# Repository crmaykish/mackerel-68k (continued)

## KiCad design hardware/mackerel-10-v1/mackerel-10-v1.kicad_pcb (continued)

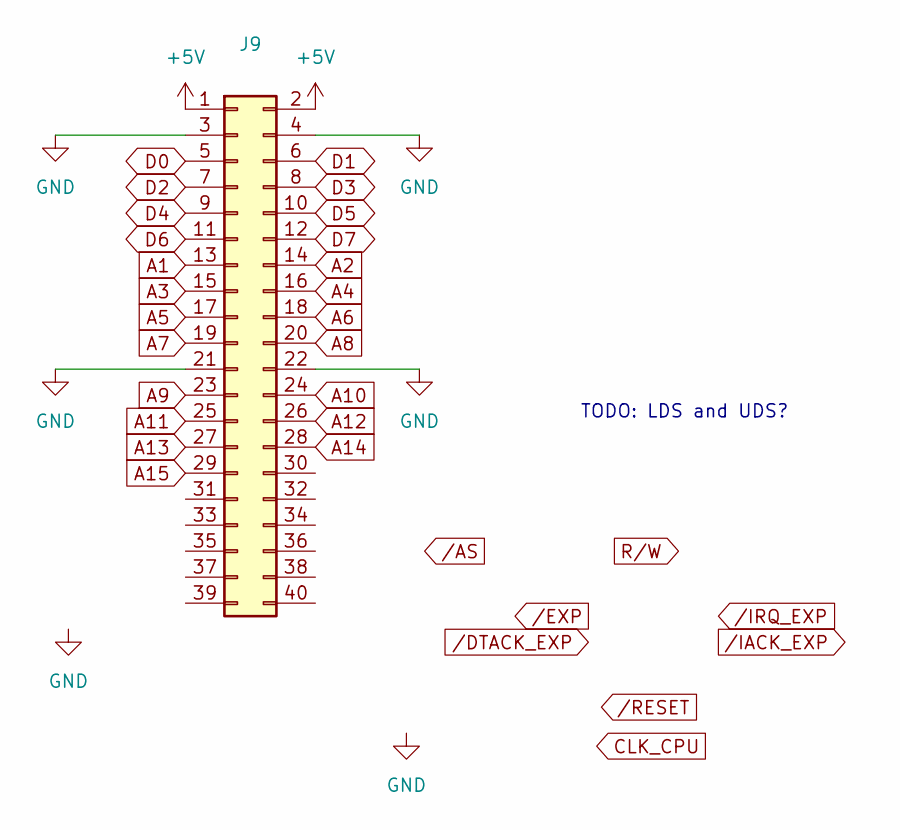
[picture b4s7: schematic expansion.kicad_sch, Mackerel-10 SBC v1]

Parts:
J9: Conn_02x20_Odd_Even; IDC-Header_2x20_P2.54mm_Vertical

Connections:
+5V: J9.1, J9.2; also elsewhere on the board
A1: J9.13; also elsewhere on the board
A2: J9.14; also elsewhere on the board
A3: J9.15; also elsewhere on the board
A4: J9.16; also elsewhere on the board
A5: J9.17; also elsewhere on the board
A6: J9.18; also elsewhere on the board
A7: J9.19; also elsewhere on the board
A8: J9.20; also elsewhere on the board
A9: J9.23; also elsewhere on the board
A10: J9.24; also elsewhere on the board
A11: J9.25; also elsewhere on the board
A12: J9.26; also elsewhere on the board
A13: J9.27; also elsewhere on the board
A14: J9.28; also elsewhere on the board
A15: J9.29; also elsewhere on the board
D0: J9.5; also elsewhere on the board
D1: J9.6; also elsewhere on the board
D2: J9.7; also elsewhere on the board
D3: J9.8; also elsewhere on the board
D4: J9.9; also elsewhere on the board
D5: J9.10; also elsewhere on the board
D6: J9.11; also elsewhere on the board
D7: J9.12; also elsewhere on the board
GND: J9.3, J9.4, J9.21, J9.22; also elsewhere on the board

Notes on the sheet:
TODO: LDS and UDS?

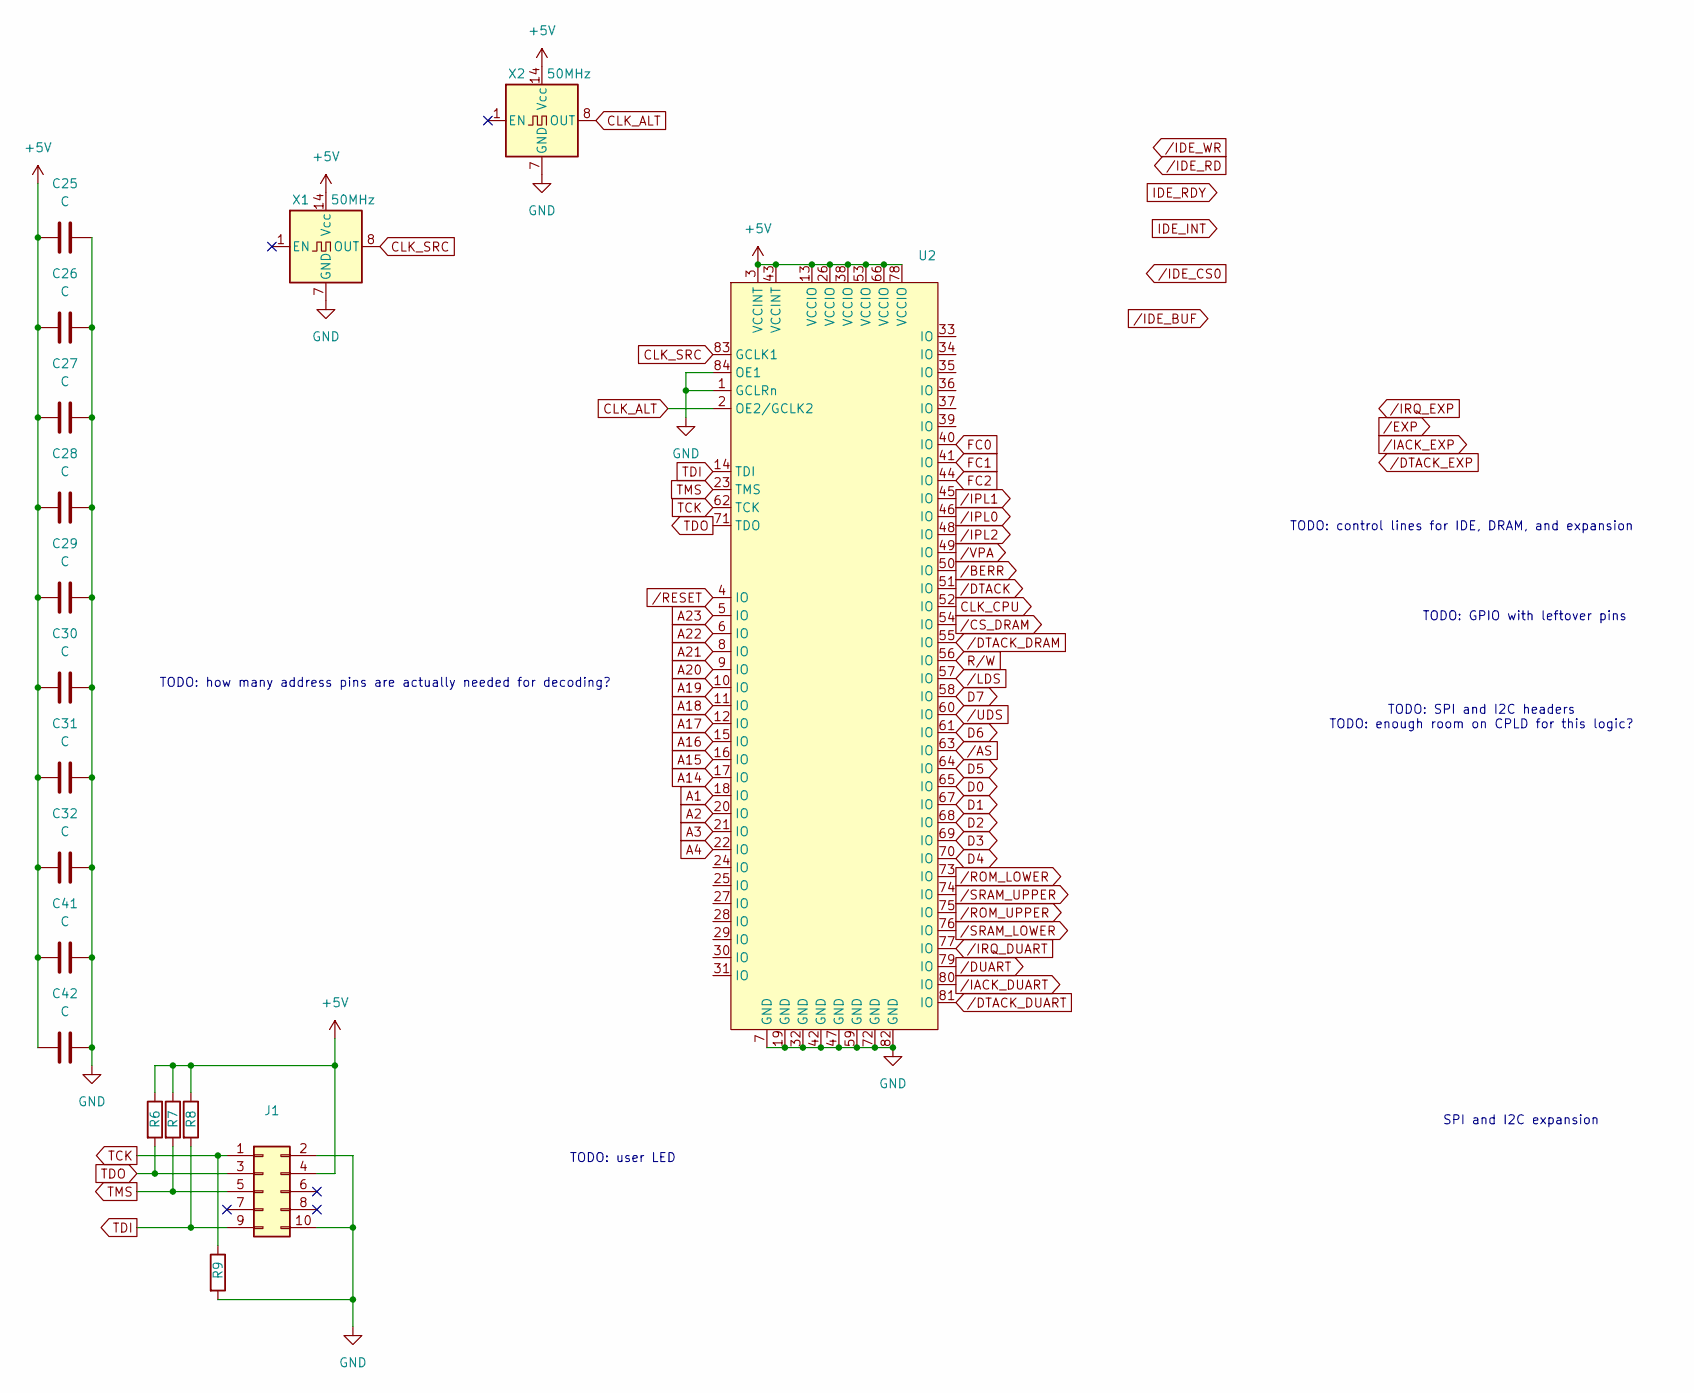
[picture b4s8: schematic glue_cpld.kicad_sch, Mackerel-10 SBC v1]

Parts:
C25, C26, C27, C28, C29, C30, C31, C32, C41, C42: C; C_Disc_D4.3mm_W1.9mm_P5.00mm
J1: Conn_02x05_Odd_Even; IDC-Header_2x05_P2.54mm_Vertical
R6, R7, R8, R9: R; R_Axial_DIN0207_L6.3mm_D2.5mm_P7.62mm_Horizontal
U2: PLCC-84_THT-Socket
X1, X2: 50MHz; Oscillator_DIP-14

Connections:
+5V: C25.1, C26.1, C27.1, C28.1, C29.2, C30.2, C31.2, C32.2, C41.2, C42.2, J1.4, R6.1, R7.1, R8.1, U2.3 (VCCINT), U2.13 (VCCIO), U2.26 (VCCIO), U2.38 (VCCIO), U2.43 (VCCINT), U2.53 (VCCIO), U2.66 (VCCIO), U2.78 (VCCIO), X1.14 (Vcc), X2.14 (Vcc); also elsewhere on the board
A1: U2.18 (IO); also elsewhere on the board
A2: U2.20 (IO); also elsewhere on the board
A3: U2.21 (IO); also elsewhere on the board
A4: U2.22 (IO); also elsewhere on the board
A14: U2.17 (IO); also elsewhere on the board
A15: U2.16 (IO); also elsewhere on the board
A16: U2.15 (IO); also elsewhere on the board
A17: U2.12 (IO); also elsewhere on the board
A18: U2.11 (IO); also elsewhere on the board
A19: U2.10 (IO); also elsewhere on the board
A20: U2.9 (IO); also elsewhere on the board
A21: U2.8 (IO); also elsewhere on the board
A22: U2.6 (IO); also elsewhere on the board
A23: U2.5 (IO); also elsewhere on the board
CLK_ALT: U2.2 (OE2/GCLK2), X2.8 (OUT); also elsewhere on the board
CLK_CPU: U2.52 (IO); also elsewhere on the board
CLK_SRC: U2.83 (GCLK1), X1.8 (OUT); also elsewhere on the board
D0: U2.65 (IO); also elsewhere on the board
D1: U2.67 (IO); also elsewhere on the board
D2: U2.68 (IO); also elsewhere on the board
D3: U2.69 (IO); also elsewhere on the board
D4: U2.70 (IO); also elsewhere on the board
D5: U2.64 (IO); also elsewhere on the board
D6: U2.61 (IO); also elsewhere on the board
D7: U2.58 (IO); also elsewhere on the board
FC0: U2.40 (IO); also elsewhere on the board
FC1: U2.41 (IO); also elsewhere on the board
FC2: U2.44 (IO); also elsewhere on the board
GND: C25.2, C26.2, C27.2, C28.2, C29.1, C30.1, C31.1, C32.1, C41.1, C42.1, J1.2, J1.10, R9.2, U2.1 (GCLRn), U2.7 (GND), U2.19 (GND), U2.32 (GND), U2.42 (GND), U2.47 (GND), U2.59 (GND), U2.72 (GND), U2.82 (GND), U2.84 (OE1), X1.7 (GND), X2.7 (GND); also elsewhere on the board
R/W: U2.56 (IO); also elsewhere on the board
TCK: J1.1, R9.1, U2.62 (TCK)
TDI: J1.9, R8.2, U2.14 (TDI)
TDO: J1.3, R6.2, U2.71 (TDO)
TMS: J1.5, R7.2, U2.23 (TMS)
/AS: U2.63 (IO); also elsewhere on the board
/BERR: U2.50 (IO); also elsewhere on the board
/CS_DRAM: U2.54 (IO); also elsewhere on the board
/DTACK: U2.51 (IO); also elsewhere on the board
/DTACK_DRAM: U2.55 (IO); also elsewhere on the board
/DTACK_DUART: U2.81 (IO); also elsewhere on the board
/DUART: U2.79 (IO); also elsewhere on the board
/IACK_DUART: U2.80 (IO); also elsewhere on the board
/IPL0: U2.46 (IO); also elsewhere on the board
/IPL1: U2.45 (IO); also elsewhere on the board
/IPL2: U2.48 (IO); also elsewhere on the board
/IRQ_DUART: U2.77 (IO); also elsewhere on the board
/LDS: U2.57 (IO); also elsewhere on the board
/RESET: U2.4 (IO); also elsewhere on the board
/ROM_LOWER: U2.73 (IO); also elsewhere on the board
/ROM_UPPER: U2.75 (IO); also elsewhere on the board
/SRAM_LOWER: U2.76 (IO); also elsewhere on the board
/SRAM_UPPER: U2.74 (IO); also elsewhere on the board
/UDS: U2.60 (IO); also elsewhere on the board
/VPA: U2.49 (IO); also elsewhere on the board

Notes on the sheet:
TODO: how many address pins are actually needed for decoding?
SPI and I2C expansion
TODO: SPI and I2C headers TODO: enough room on CPLD for this logic?
TODO: GPIO with leftover pins
TODO: user LED
TODO: control lines for IDE, DRAM, and expansion

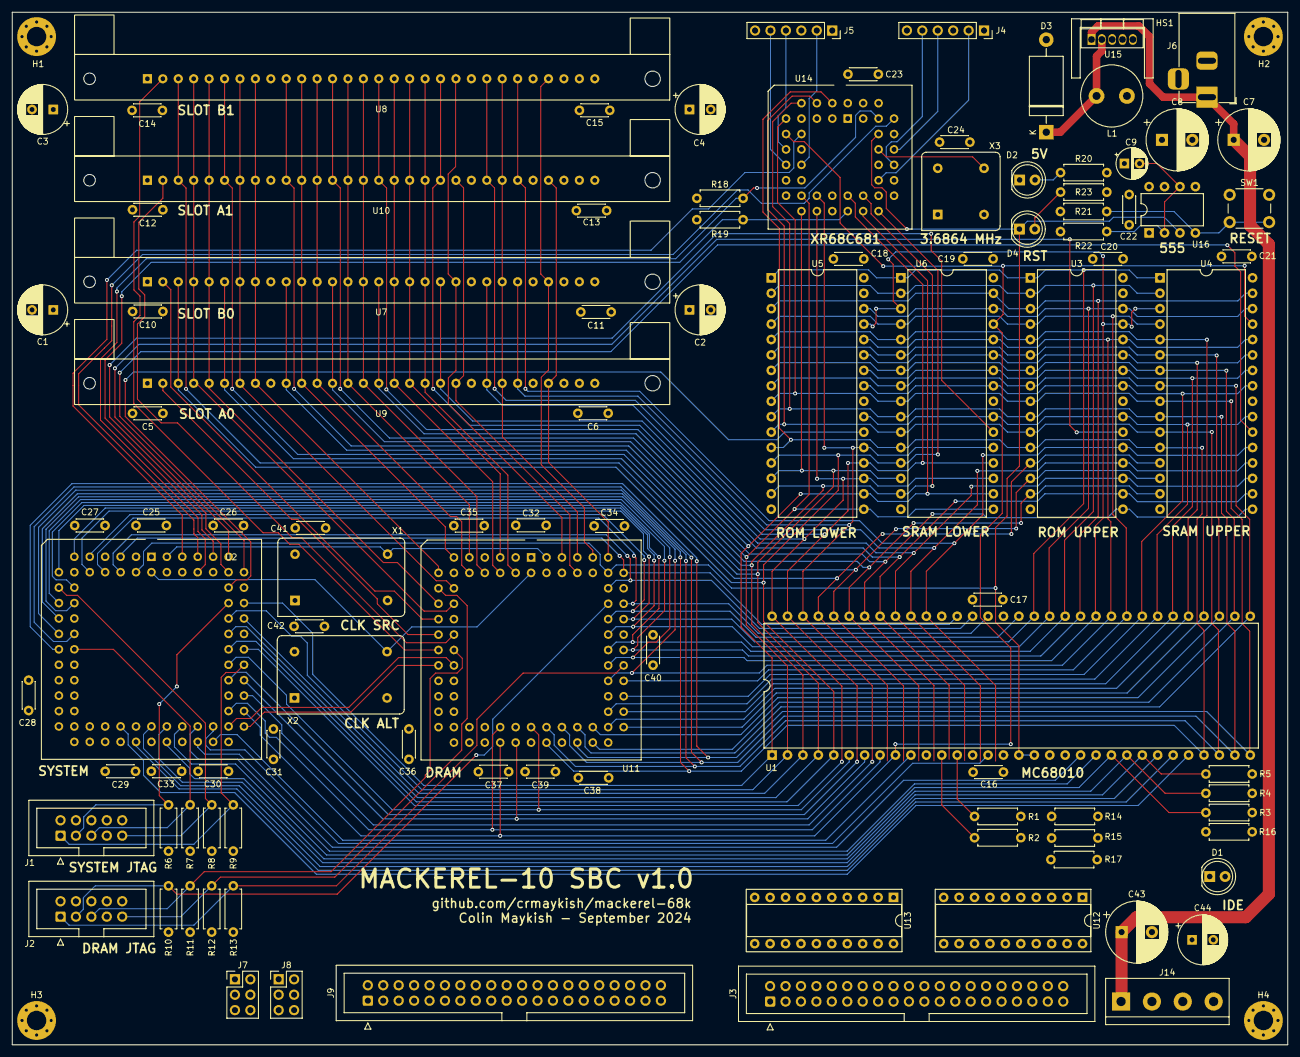
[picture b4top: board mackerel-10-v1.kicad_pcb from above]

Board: 4 copper layers, 210.0 x 170.0 mm, 107 parts (0 on the bottom side), 133 nets.

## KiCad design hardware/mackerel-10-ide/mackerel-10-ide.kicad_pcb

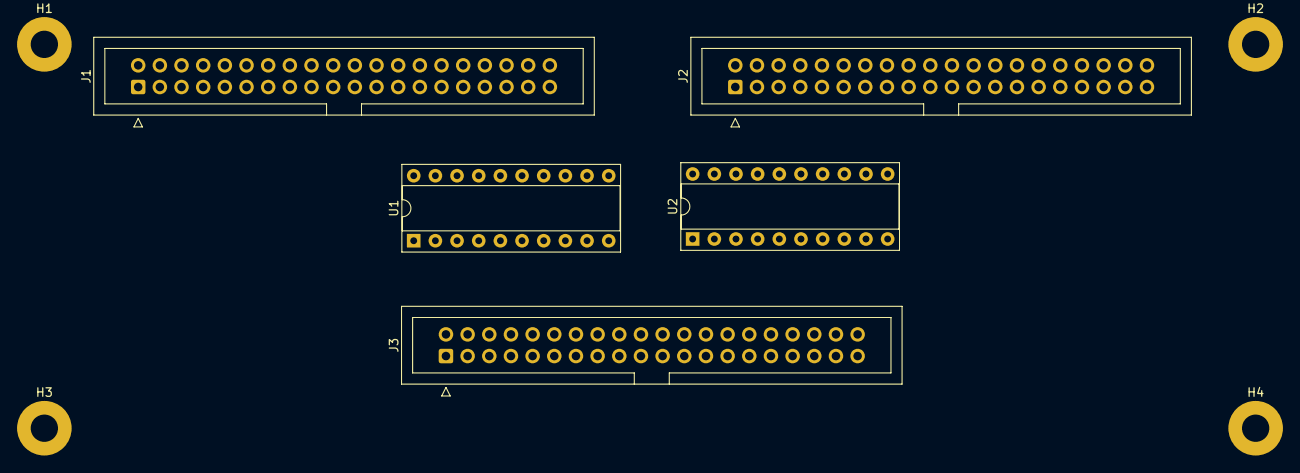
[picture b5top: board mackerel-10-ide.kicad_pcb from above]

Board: 2 copper layers, 9 parts (0 on the bottom side), 40 nets, no tracks yet.

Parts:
H1, H2, H3, H4: MountingHole_Pad; MountingHole_3.2mm_M3_Pad
J1, J2, J3: Conn_02x20_Odd_Even; IDC-Header_2x20_P2.54mm_Vertical
U1, U2: 74HC245; DIP-20_W7.62mm_Socket

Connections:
+5V: J1.1, J1.2, J2.1, J2.2, U1.20 (VCC), U2.20 (VCC)
A1: J1.13, J3.35
A2: J1.14, J3.33
A3: J1.15, J3.36
D0: J2.5, U2.2 (A0)
D1: J2.6, U2.3 (A1)
D2: J2.7, U2.4 (A2)
D3: J2.8, U2.5 (A3)
D4: J2.9, U2.6 (A4)
D5: J2.10, U2.7 (A5)
D6: J2.11, U2.8 (A6)
D7: J2.12, U2.9 (A7)
D8: J1.5, U1.9 (A7)
D9: J1.6, U1.8 (A6)
D10: J1.7, U1.7 (A5)
D11: J1.8, U1.6 (A4)
D12: J1.9, U1.5 (A3)
D13: J1.10, U1.4 (A2)
D14: J1.11, U1.3 (A1)
D15: J1.12, U1.2 (A0)
GND: H1.1, H2.1, H3.1, H4.1, J1.3, J1.4, J1.21, J1.22, J1.38, J1.39, J1.40, J2.3, J2.4, J2.23, J2.24, J2.33, J2.34, J2.39, J2.40, J3.2, J3.19, J3.22, J3.24, J3.26, J3.30, J3.40, U1.10 (GND), U2.10 (GND)
IDE_D0: J3.17, U1.11 (B7)
IDE_D1: J3.15, U1.12 (B6)
IDE_D2: J3.13, U1.13 (B5)
IDE_D3: J3.11, U1.14 (B4)
IDE_D4: J3.9, U1.15 (B3)
IDE_D5: J3.7, U1.16 (B2)
IDE_D6: J3.5, U1.17 (B1)
IDE_D7: J3.3, U1.18 (B0)
IDE_D8: J3.4, U2.18 (B0)
IDE_D9: J3.6, U2.17 (B1)
IDE_D10: J3.8, U2.16 (B2)
IDE_D11: J3.10, U2.15 (B3)
IDE_D12: J3.12, U2.14 (B4)
IDE_D13: J3.14, U2.13 (B5)
IDE_D14: J3.16, U2.12 (B6)
IDE_D15: J3.18, U2.11 (B7)
R/W: J2.14, U1.1 (A->B), U2.1 (A->B)
/IDE_BUF: U1.19 (CE), U2.19 (CE)
/RESET: J2.37, J2.38, J3.1

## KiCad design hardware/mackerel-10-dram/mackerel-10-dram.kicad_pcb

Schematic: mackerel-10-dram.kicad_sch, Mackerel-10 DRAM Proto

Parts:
C1, C2: 1000uF; CP_Radial_D8.0mm_P3.50mm
C3, C4, C5, C6, C7, C8, C9, C10: 0.1uF; C_Disc_D4.7mm_W2.5mm_P5.00mm
D1: LED; LED_D5.0mm
H1, H2, H3, H4: MountingHole_Pad; MountingHole_3.2mm_M3_Pad
J1, J2: Conn_02x20_Odd_Even; IDC-Header_2x20_P2.54mm_Vertical
J3: Conn_02x05_Odd_Even; IDC-Header_2x05_P2.54mm_Vertical
J4, J5: Conn_01x30; PinHeader_1x30_P2.54mm_Vertical
J6: Conn_01x10; PinSocket_1x10_P2.54mm_Vertical
R1, R2, R3, R4, R5: R; R_Axial_DIN0207_L6.3mm_D2.5mm_P7.62mm_Horizontal
R6, R7, R8, R9, R10, R11, R12, R13, R14, R15, R16, R17, R18, R19, R20, R21: 22; R_Axial_DIN0207_L6.3mm_D2.5mm_P2.54mm_Vertical
U1, U2: SIMM-30
U3: PLCC-84_THT-Socket

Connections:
+5V: C1.1, C2.1, C3.1, C4.1, C5.1, C6.1, C7.1, C8.1, C9.1, C10.1, J1.1, J1.2, J2.1, J2.2, J3.4, J4.1, J4.30, J5.1, J5.30, J6.9, R1.1, R2.1, R3.1, R5.1, U1.1 (VCC), U1.30 (VCC), U2.1 (VCC), U2.30 (VCC), U3.3 (VCCINT), U3.13 (VCCIO), U3.26 (VCCIO), U3.38 (VCCIO), U3.43 (VCCINT), U3.53 (VCCIO), U3.66 (VCCIO), U3.78 (VCCIO)
A1: J1.13, U3.52 (IO)
A2: J1.14, U3.51 (IO)
A3: J1.15, U3.50 (IO)
A4: J1.16, U3.49 (IO)
A5: J1.17, U3.48 (IO)
A6: J1.18, U3.46 (IO)
A7: J1.19, U3.45 (IO)
A8: J1.20, U3.44 (IO)
A9: J1.27, U3.12 (IO)
A10: J1.28, U3.15 (IO)
A11: J1.29, U3.11 (IO)
A12: J1.30, U3.9 (IO)
A13: J1.31, U3.10 (IO)
A14: J1.32, U3.8 (IO)
A15: J1.33, U3.5 (IO)
A16: J1.34, U3.6 (IO)
A17: J1.35, U3.4 (IO)
A18: J1.36, U3.81 (IO)
A19: J1.37, U3.79 (IO)
A20: J1.26, U3.17 (IO)
A21: J1.25, U3.16 (IO)
A22: J1.24, U3.18 (IO)
A23: J1.23, U3.21 (IO)
CAS0: J4.2, U1.2 (/CAS), U3.55 (IO)
CAS1: J5.2, U2.2 (/CAS), U3.56 (IO)
CLK_CPU: J2.35
CLK_SRC: J2.36, U3.83 (GCLK1)
D0: J2.5, R13.2
D1: J2.6, R12.2
D2: J2.7, R11.2
D3: J2.8, R10.2
D4: J2.9, R9.2
D5: J2.10, R8.2
D6: J2.11, R7.2
D7: J2.12, R6.2
D8: J1.5, R14.2
D9: J1.6, R15.2
D10: J1.7, R16.2
D11: J1.8, R17.2
D12: J1.9, R18.2
D13: J1.10, R19.2
D14: J1.11, R20.2
D15: J1.12, R21.2
GND: C1.2, C2.2, C3.2, C4.2, C5.2, C6.2, C7.2, C8.2, C9.2, C10.2, D1.1 (K), H1.1, H2.1, H3.1, H4.1, J1.3, J1.4, J1.21, J1.22, J1.38, J1.39, J1.40, J2.3, J2.4, J2.23, J2.24, J2.33, J2.34, J2.39, J2.40, J3.2, J3.10, J4.9, J4.22, J5.9, J5.22, J6.10, R4.2, U1.9 (GND), U1.22 (GND), U2.9 (GND), U2.22 (GND), U3.1 (GCLRn), U3.2 (OE2/GCLK2), U3.7 (GND), U3.19 (GND), U3.32 (GND), U3.42 (GND), U3.47 (GND), U3.59 (GND), U3.72 (GND), U3.82 (GND), U3.84 (OE1)
GPIO_0: J2.25
GPIO_1: J2.26
GPIO_2: J2.27
GPIO_3: J2.28
GPIO_4: J2.29
GPIO_5: J2.30
GPIO_6: J2.31
GPIO_7: J2.32
unnamed: D1.2 (A), R5.2
unnamed: J6.1, U3.22 (IO)
unnamed: J6.2, U3.24 (IO)
unnamed: J6.3, U3.25 (IO)
unnamed: J6.4, U3.27 (IO)
unnamed: J6.5, U3.28 (IO)
unnamed: J6.6, U3.29 (IO)
unnamed: J6.7, U3.30 (IO)
unnamed: J6.8, U3.31 (IO)
RAMWR: J4.21, J5.21, U1.21 (/WE), U2.21 (/WE), U3.57 (IO)
RAM_A0: J4.4, J5.4, U1.4 (A0), U2.4 (A0), U3.58 (IO)
RAM_A1: J4.5, J5.5, U1.5 (A1), U2.5 (A1), U3.60 (IO)
RAM_A2: J4.7, J5.7, U1.7 (A2), U2.7 (A2), U3.61 (IO)
RAM_A3: J4.8, J5.8, U1.8 (A3), U2.8 (A3), U3.63 (IO)
RAM_A4: J4.11, J5.11, U1.11 (A4), U2.11 (A4), U3.64 (IO)
RAM_A5: J4.12, J5.12, U1.12 (A5), U2.12 (A5), U3.65 (IO)
RAM_A6: J4.14, J5.14, U1.14 (A6), U2.14 (A6), U3.67 (IO)
RAM_A7: J4.15, J5.15, U1.15 (A7), U2.15 (A7), U3.68 (IO)
RAM_A8: J4.17, J5.17, U1.17 (A8), U2.17 (A8), U3.69 (IO)
RAM_A9: J4.18, J5.18, U1.18 (A9), U2.18 (A9), U3.70 (IO)
RAM_A10: J4.19, J5.19, U1.19 (A10), U2.19 (A10), U3.73 (IO)
RAM_A11: J4.24, J5.24, U1.24 (A11), U2.24 (A11), U3.74 (IO)
RAM_D0: J4.3, R6.1, U1.3 (DQ0)
RAM_D1: J4.6, R7.1, U1.6 (DQ1)
RAM_D2: J4.10, R8.1, U1.10 (DQ2)
RAM_D3: J4.13, R9.1, U1.13 (DQ3)
RAM_D4: J4.16, R10.1, U1.16 (DQ4)
RAM_D5: J4.20, R11.1, U1.20 (DQ5)
RAM_D6: J4.23, R12.1, U1.23 (DQ6)
RAM_D7: J4.25, R13.1, U1.25 (DQ7)
RAM_D8: J5.3, R14.1, U2.3 (DQ0)
RAM_D9: J5.6, R15.1, U2.6 (DQ1)
RAM_D10: J5.10, R16.1, U2.10 (DQ2)
RAM_D11: J5.13, R17.1, U2.13 (DQ3)
RAM_D12: J5.16, R18.1, U2.16 (DQ4)
RAM_D13: J5.20, R19.1, U2.20 (DQ5)
RAM_D14: J5.23, R20.1, U2.23 (DQ6)
RAM_D15: J5.25, R21.1, U2.25 (DQ7)
RAS: J4.27, J5.27, U1.27 (/RAS), U2.27 (/RAS), U3.54 (IO)
R/W: J2.14, U3.76 (IO)
TCK: J3.1, R4.1, U3.62 (TCK)
TDI: J3.9, R3.2, U3.14 (TDI)
TDO: J3.3, R1.2, U3.71 (TDO)
TMS: J3.5, R2.2, U3.23 (TMS)
/AS: J2.13, U3.75 (IO)
/BERR: J2.17
/DTACK_EXP: J2.21, U3.40 (IO)
/EXP: J2.19, U3.41 (IO)
/IACK_EXP: J2.22
/IRQ_EXP: J2.20
/LDS: J2.16, U3.77 (IO)
/RESET: J2.37, J2.38, U3.20 (IO)
/UDS: J2.15, U3.80 (IO)
/VPA: J2.18

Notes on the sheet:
NOTE: data lines are reversed to facilitate routing

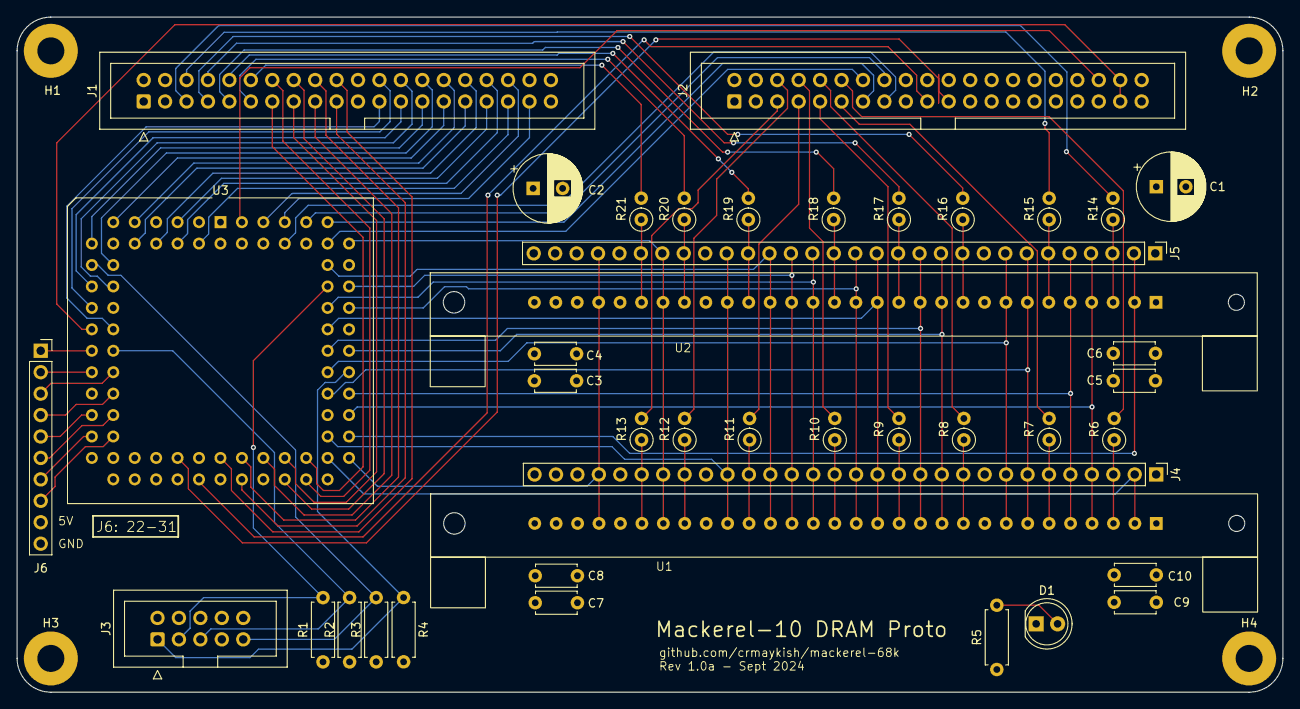
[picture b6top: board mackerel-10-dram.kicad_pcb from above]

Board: 4 copper layers, 150.0 x 80.0 mm, 45 parts (0 on the bottom side), 94 nets.

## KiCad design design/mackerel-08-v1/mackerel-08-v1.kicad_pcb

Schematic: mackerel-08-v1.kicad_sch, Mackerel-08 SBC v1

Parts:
J1: Conn_02x20_Odd_Even; IDC-Header_2x20_P2.54mm_Vertical
JP1: Jumper_2_Open; PinHeader_1x02_P2.54mm_Vertical
R1, R2, R3, R4, R5, R6, R7, R18, R19, R20: R; R_Axial_DIN0207_L6.3mm_D2.5mm_P7.62mm_Horizontal
U1: MC68008; PLCC-52_THT-Socket
U2: 74HC595; DIP-16_W7.62mm
U3, U4, U5: ATF22V10C; DIP-24_W7.62mm
X1: CXO_DIP8; Oscillator_DIP-8

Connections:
/CLK_CPU: U1.38 (CLK), X1.5 (OUT)
A0: J1.13, U1.51 (A0); also elsewhere on the board
A1: J1.14, U1.52 (A1), U4.10 (IN9); also elsewhere on the board
A2: J1.15, U1.1 (A2), U4.11 (IN10); also elsewhere on the board
A3: J1.16, U1.2 (A3), U4.13 (IN11); also elsewhere on the board
A4: J1.17, U1.3 (A4); also elsewhere on the board
A5: J1.18, U1.4 (A5); also elsewhere on the board
A6: J1.19, U1.5 (A6); also elsewhere on the board
A7: J1.20, U1.6 (A7); also elsewhere on the board
A8: J1.23, U1.7 (A8); also elsewhere on the board
A9: J1.24, U1.8 (A9); also elsewhere on the board
A10: J1.25, U1.9 (A10); also elsewhere on the board
A11: J1.26, U1.10 (A11); also elsewhere on the board
A12: J1.27, U1.11 (A12); also elsewhere on the board
A13: J1.28, U1.12 (A13), U3.4 (IN3/PD); also elsewhere on the board
A14: J1.29, U1.14 (A14), U3.5 (IN4); also elsewhere on the board
A15: J1.30, U1.16 (A15), U3.6 (IN5); also elsewhere on the board
A16: U1.18 (A16), U3.7 (IN6); also elsewhere on the board
A17: U1.19 (A17), U3.8 (IN7); also elsewhere on the board
A18: U1.20 (A18), U3.9 (IN8); also elsewhere on the board
A19: U1.21 (A19), U3.10 (IN9)
A20: U1.22 (A20), U3.11 (IN10)
A21: U1.13 (A21), U3.13 (IN11)
AS: U4.17 (IO3), U5.1 (CLK/IN0)
BOOT: U2.7 (QH), U3.1 (CLK/IN0)
D0: J1.5, U1.30 (D0); also elsewhere on the board
D1: J1.6, U1.29 (D1); also elsewhere on the board
D2: J1.7, U1.28 (D2); also elsewhere on the board
D3: J1.8, U1.27 (D3); also elsewhere on the board
D4: J1.9, U1.26 (D4); also elsewhere on the board
D5: J1.10, U1.25 (D5); also elsewhere on the board
D6: J1.11, U1.24 (D6); also elsewhere on the board
D7: J1.12, U1.23 (D7); also elsewhere on the board
FC0: U1.50 (FC0), U4.1 (CLK/IN0)
FC1: U1.49 (FC1), U4.2 (IN1)
FC2: U1.48 (FC2), U4.3 (IN2)
GND: J1.3, J1.4, J1.21, J1.22, J1.39, J1.40, R18.2, U1.17 (GND), U1.39 (GND), U2.8 (GND), U2.13 (~OE), U3.12 (GND), U4.7 (IN6), U4.8 (IN7), U4.9 (IN8), U4.12 (GND), U5.4 (IN3/PD), U5.10 (IN9), U5.11 (IN10), U5.12 (GND), U5.13 (IN11), X1.4 (GND); also elsewhere on the board
unnamed: JP1.1 (A), U5.23 (IO9)
unnamed: R6.1, U1.44 (/BERR)
unnamed: R5.1, U1.36 (/BGACK)
unnamed: R4.1, U1.37 (/BR)
unnamed: R7.1, U1.43 (/VPA)
/AS: J1.33, U1.31 (/AS), U2.11 (SRCLK), U2.12 (RCLK), U3.2 (IN1), U4.4 (IN3/PD)
/DS: J1.34, U1.32 (/DS)
/DTACK_CPU: JP1.2 (B), R18.1, U1.34 (/DTACK)
/DTACK_DUART: U5.6 (IN5); also elsewhere on the board
/DTACK_EXP: J1.37, U5.7 (IN6)
/DUART: U3.23 (IO9), U5.3 (IN2); also elsewhere on the board
/EXP: J1.35, U3.14 (IO0), U5.5 (IN4)
/IACK: U3.3 (IN2), U4.23 (IO9)
/IACK_DUART: U4.19 (IO5), U5.9 (IN8); also elsewhere on the board
/IACK_EXP: J1.38, U4.18 (IO4), U5.8 (IN7)
/IPL0: R1.2, U1.47 (/IPL0), U4.22 (IO8)
/IPL1: R2.2, U1.45 (/IPL1), U4.21 (IO7)
/IPL2: R3.2, U1.46 (/IPL2), U4.20 (IO6)
/IRQ_DUART: R19.2, U4.5 (IN4); also elsewhere on the board
/IRQ_EXP: J1.36, R20.2, U4.6 (IN5)
/RAM0: U3.21 (IO7); also elsewhere on the board
/RAM1: U3.20 (IO6); also elsewhere on the board
/RAM2: U3.19 (IO5); also elsewhere on the board
/RAM3: U3.18 (IO4); also elsewhere on the board
/RAM4: U3.17 (IO3); also elsewhere on the board
/RAM5: U3.16 (IO2); also elsewhere on the board
/RAM6: U3.15 (IO1); also elsewhere on the board
/RESET: J1.31, U1.40 (/HALT), U1.41 (/RESET), U2.10 (~SRCLR); also elsewhere on the board
/ROM: U3.22 (IO8), U5.2 (IN1); also elsewhere on the board
/RW: J1.32, U1.33 (/RW); also elsewhere on the board

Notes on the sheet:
Expansion Bus
DTACK Decoder / Wait States
MC68008 CPU
Inverted /AS
TODO: double check the pinout here
BOOT Signal
Interrupt Decoder
Address Decoder
Open for DTACK grounded Closed for DTACK control

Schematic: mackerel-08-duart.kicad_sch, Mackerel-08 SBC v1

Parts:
D1: LED; LED_D5.0mm
J2, J3: Conn_01x06; PinSocket_1x06_P2.54mm_Horizontal
J5, J6, J7: Conn_02x04_Odd_Even; IDC-Header_2x04_P2.54mm_Vertical
R8, R9, R10, R11, R12, R13, R28, R29: R; R_Axial_DIN0207_L6.3mm_D2.5mm_P7.62mm_Horizontal
U15: XR68C681; PLCC-44_THT-Socket
X2: CXO_DIP8; Oscillator_DIP-8

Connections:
A1: U15.2 (A1); also elsewhere on the board
A2: U15.4 (A2); also elsewhere on the board
A3: U15.6 (A3); also elsewhere on the board
A4: U15.7 (A4); also elsewhere on the board
D0: U15.28 (D0); also elsewhere on the board
D1: U15.18 (D1); also elsewhere on the board
D2: U15.27 (D2); also elsewhere on the board
D3: U15.19 (D3); also elsewhere on the board
D4: U15.26 (D4); also elsewhere on the board
D5: U15.20 (D5); also elsewhere on the board
D6: U15.25 (D6); also elsewhere on the board
D7: U15.21 (D7); also elsewhere on the board
GND: D1.1 (K), J2.1, J3.1, J5.7, J5.8, J6.7, J6.8, J7.7, J7.8, R28.1, R29.1, U15.22 (GND), X2.4 (GND); also elsewhere on the board
unnamed: D1.2 (A), R13.2
unnamed: R11.1, U15.42 (IP5)
unnamed: R13.1, U15.17 (OP7)
unnamed: U15.36 (X1/CLK), X2.5 (OUT)
RXA: J2.4, U15.35 (RXDA)
RXB: J3.4, U15.11 (RXDB)
SPI_CLK: J5.2, J6.2, J7.2, U15.15 (OP3)
SPI_CS0: J5.4, U15.30 (OP4)
SPI_CS1: J6.4, U15.16 (OP5)
SPI_CS2: J7.4, U15.29 (OP6)
SPI_DI: J5.3, J6.3, J7.3, U15.31 (OP2)
SPI_DO: J5.5, J6.5, J7.5, R10.1, U15.43 (IP4)
SPI_INT0: J5.6, R8.1, U15.40 (IP2)
SPI_INT1: J6.6, R9.1, U15.3 (IP3)
TXA: J2.5, U15.33 (TXDA)
TXB: J3.5, U15.13 (TXDB)
/CTSA: R28.2, U15.8 (IP0)
/CTSB: R29.2, U15.5 (IP1)
/DTACK_DUART: U15.10 (/DTACK); also elsewhere on the board
/DUART: U15.39 (CS); also elsewhere on the board
/IACK_DUART: R12.1, U15.41 (/IACK); also elsewhere on the board
/IRQ_DUART: U15.24 (INTR); also elsewhere on the board
/RESET: U15.38 (/RESET); also elsewhere on the board
/RTSA: J2.2, U15.32 (OP0)
/RTSB: J3.2, U15.14 (OP1)
/RW: U15.9 (/RW); also elsewhere on the board

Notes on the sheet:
SPI interrupts are assumed active-low
No int on SPI2
XR68C681 DUART
SPI Headers
UART Headers

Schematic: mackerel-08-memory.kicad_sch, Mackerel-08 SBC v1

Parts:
U6, U7, U8, U9, U10, U11, U12: AS6C4008-55PCN; DIP-32_W15.24mm
U13: SST39SF040; DIP_Socket-32_W11.9_W12.7_W15.24_W17.78_W18.5_3M_232-1285-0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

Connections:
A0: U6.12 (A0), U7.12 (A0), U8.12 (A0), U9.12 (A0), U10.12 (A0), U11.12 (A0), U12.12 (A0), U13.12 (A0); also elsewhere on the board
A1: U6.11 (A1), U7.11 (A1), U8.11 (A1), U9.11 (A1), U10.11 (A1), U11.11 (A1), U12.11 (A1), U13.11 (A1); also elsewhere on the board
A2: U6.10 (A2), U7.10 (A2), U8.10 (A2), U9.10 (A2), U10.10 (A2), U11.10 (A2), U12.10 (A2), U13.10 (A2); also elsewhere on the board
A3: U6.9 (A3), U7.9 (A3), U8.9 (A3), U9.9 (A3), U10.9 (A3), U11.9 (A3), U12.9 (A3), U13.9 (A3); also elsewhere on the board
A4: U6.8 (A4), U7.8 (A4), U8.8 (A4), U9.8 (A4), U10.8 (A4), U11.8 (A4), U12.8 (A4), U13.8 (A4); also elsewhere on the board
A5: U6.7 (A5), U7.7 (A5), U8.7 (A5), U9.7 (A5), U10.7 (A5), U11.7 (A5), U12.7 (A5), U13.7 (A5); also elsewhere on the board
A6: U6.6 (A6), U7.6 (A6), U8.6 (A6), U9.6 (A6), U10.6 (A6), U11.6 (A6), U12.6 (A6), U13.6 (A6); also elsewhere on the board
A7: U6.5 (A7), U7.5 (A7), U8.5 (A7), U9.5 (A7), U10.5 (A7), U11.5 (A7), U12.5 (A7), U13.5 (A7); also elsewhere on the board
A8: U6.27 (A8), U7.27 (A8), U8.27 (A8), U9.27 (A8), U10.27 (A8), U11.27 (A8), U12.27 (A8), U13.27 (A8); also elsewhere on the board
A9: U6.26 (A9), U7.26 (A9), U8.26 (A9), U9.26 (A9), U10.26 (A9), U11.26 (A9), U12.26 (A9), U13.26 (A9); also elsewhere on the board
A10: U6.23 (A10), U7.23 (A10), U8.23 (A10), U9.23 (A10), U10.23 (A10), U11.23 (A10), U12.23 (A10), U13.23 (A10); also elsewhere on the board
A11: U6.25 (A11), U7.25 (A11), U8.25 (A11), U9.25 (A11), U10.25 (A11), U11.25 (A11), U12.25 (A11), U13.25 (A11); also elsewhere on the board
A12: U6.4 (A12), U7.4 (A12), U8.4 (A12), U9.4 (A12), U10.4 (A12), U11.4 (A12), U12.4 (A12), U13.4 (A12); also elsewhere on the board
A13: U6.28 (A13), U7.28 (A13), U8.28 (A13), U9.28 (A13), U10.28 (A13), U11.28 (A13), U12.28 (A13), U13.28 (A13); also elsewhere on the board
A14: U6.3 (A14), U7.3 (A14), U8.3 (A14), U9.3 (A14), U10.3 (A14), U11.3 (A14), U12.3 (A14), U13.29 (A14); also elsewhere on the board
A15: U6.31 (A15), U7.31 (A15), U8.31 (A15), U9.31 (A15), U10.31 (A15), U11.31 (A15), U12.31 (A15), U13.3 (A15); also elsewhere on the board
A16: U6.2 (A16), U7.2 (A16), U8.2 (A16), U9.2 (A16), U10.2 (A16), U11.2 (A16), U12.2 (A16), U13.2 (A16); also elsewhere on the board
A17: U6.30 (A17), U7.30 (A17), U8.30 (A17), U9.30 (A17), U10.30 (A17), U11.30 (A17), U12.30 (A17), U13.30 (A17); also elsewhere on the board
A18: U6.1 (A18), U7.1 (A18), U8.1 (A18), U9.1 (A18), U10.1 (A18), U11.1 (A18), U12.1 (A18), U13.1 (A18); also elsewhere on the board
D0: U6.13 (DQ0), U7.13 (DQ0), U8.13 (DQ0), U9.13 (DQ0), U10.13 (DQ0), U11.13 (DQ0), U12.13 (DQ0), U13.13 (D0); also elsewhere on the board
D1: U6.14 (DQ1), U7.14 (DQ1), U8.14 (DQ1), U9.14 (DQ1), U10.14 (DQ1), U11.14 (DQ1), U12.14 (DQ1), U13.14 (D1); also elsewhere on the board
D2: U6.15 (DQ2), U7.15 (DQ2), U8.15 (DQ2), U9.15 (DQ2), U10.15 (DQ2), U11.15 (DQ2), U12.15 (DQ2), U13.15 (D2); also elsewhere on the board
D3: U6.17 (DQ3), U7.17 (DQ3), U8.17 (DQ3), U9.17 (DQ3), U10.17 (DQ3), U11.17 (DQ3), U12.17 (DQ3), U13.17 (D3); also elsewhere on the board
D4: U6.18 (DQ4), U7.18 (DQ4), U8.18 (DQ4), U9.18 (DQ4), U10.18 (DQ4), U11.18 (DQ4), U12.18 (DQ4), U13.18 (D4); also elsewhere on the board
D5: U6.19 (DQ5), U7.19 (DQ5), U8.19 (DQ5), U9.19 (DQ5), U10.19 (DQ5), U11.19 (DQ5), U12.19 (DQ5), U13.19 (D5); also elsewhere on the board
D6: U6.20 (DQ6), U7.20 (DQ6), U8.20 (DQ6), U9.20 (DQ6), U10.20 (DQ6), U11.20 (DQ6), U12.20 (DQ6), U13.20 (D6); also elsewhere on the board
D7: U6.21 (DQ7), U7.21 (DQ7), U8.21 (DQ7), U9.21 (DQ7), U10.21 (DQ7), U11.21 (DQ7), U12.21 (DQ7), U13.21 (D7); also elsewhere on the board
GND: U6.16 (VSS), U6.24 (OE#), U7.16 (VSS), U7.24 (OE#), U8.16 (VSS), U8.24 (OE#), U9.16 (VSS), U9.24 (OE#), U10.16 (VSS), U10.24 (OE#), U11.16 (VSS), U11.24 (OE#), U12.16 (VSS), U12.24 (OE#), U13.16 (GND), U13.24 (/OE); also elsewhere on the board
/RAM0: U6.22 (CE#); also elsewhere on the board
/RAM1: U7.22 (CE#); also elsewhere on the board
/RAM2: U8.22 (CE#); also elsewhere on the board
/RAM3: U9.22 (CE#); also elsewhere on the board
/RAM4: U10.22 (CE#); also elsewhere on the board
/RAM5: U11.22 (CE#); also elsewhere on the board
/RAM6: U12.22 (CE#); also elsewhere on the board
/ROM: U13.22 (/CE); also elsewhere on the board
/RW: U6.29 (WE#), U7.29 (WE#), U8.29 (WE#), U9.29 (WE#), U10.29 (WE#), U11.29 (WE#), U12.29 (WE#); also elsewhere on the board

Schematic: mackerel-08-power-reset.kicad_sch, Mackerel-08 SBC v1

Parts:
C10: C_Polarized; CP_Radial_D5.0mm_P2.50mm
C11, C12, C13, C14, C15, C16, C17, C18, C19, C20, C21, C23, C24, C26, C27, C28, C29: C; C_Disc_D4.3mm_W1.9mm_P5.00mm
C22, C25: C_Polarized; CP_Radial_D10.0mm_P5.00mm
D2, D3: LED; LED_D5.0mm
H1, H2, H3, H4: MountingHole; MountingHole_3.2mm_M3_Pad
J9: DC_Jack; BarrelJack_GCT_DCJ200-10-A_Horizontal
R14, R15, R16, R17: R; R_Axial_DIN0207_L6.3mm_D2.5mm_P7.62mm_Horizontal
SW1: SW_Push; SW_PUSH_6mm_H5mm
SW2: SW_SPDT; SW_Mini_Toggle
U17: NE555P; DIP-8_W7.62mm

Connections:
GND: C11.2, C12.2, C13.2, C14.2, C15.2, C16.2, C17.2, C18.2, C19.2, C20.2, C21.2, C22.2, C23.2, C24.2, C25.2, C26.2, C27.2, C28.2, C29.2, D3.1 (K), H1.1, H2.1, H3.1, H4.1, J9.2 (GND), R15.2, SW1.1, U17.1 (GND); also elsewhere on the board
unnamed: D2.2 (A), R14.2
unnamed: D3.2 (A), R17.2
unnamed: J9.1 (VCC), SW2.2 (B)
unnamed: R16.2, SW1.2, U17.4 (R)
unnamed: C10.2, R15.1, U17.2 (TR), U17.6 (THR)
/RESET: D2.1 (K), U17.3 (Q); also elsewhere on the board

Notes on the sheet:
Power-on Reset
Power In

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
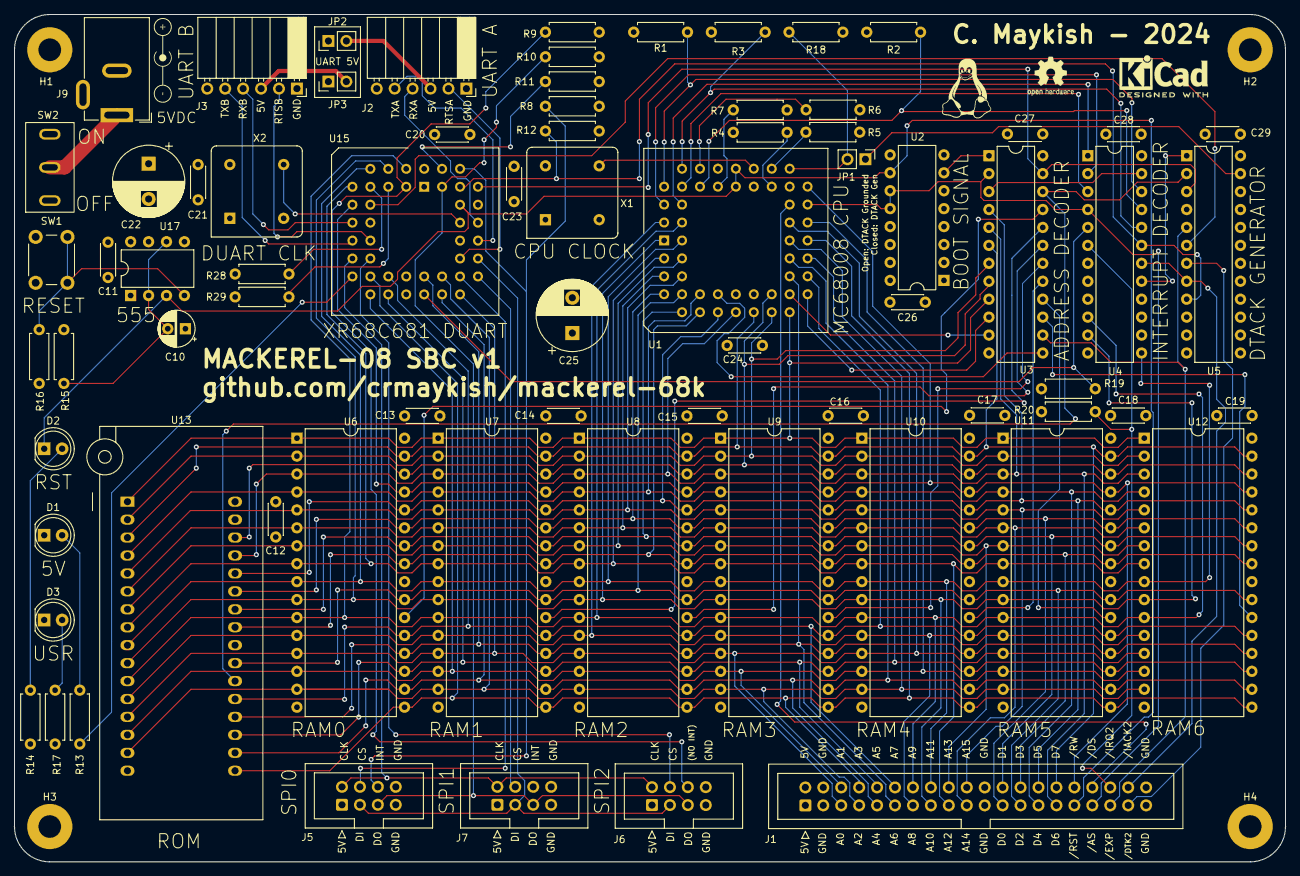
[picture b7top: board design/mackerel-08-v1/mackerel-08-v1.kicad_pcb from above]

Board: 4 copper layers, 180.0 x 120.0 mm, 78 parts (0 on the bottom side), 95 nets.

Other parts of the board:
JP2, JP3: Jumper_2_Open; PinHeader_1x02_P2.54mm_Vertical

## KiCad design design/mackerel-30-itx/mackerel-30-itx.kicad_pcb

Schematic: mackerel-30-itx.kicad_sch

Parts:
H1, H2, H3, H4: MountingHole_Pad; MountingHole_3.2mm_M3_Pad_Via
J1, J2: DE9_Plug_MountingHoles; DSUB-9_Female_Horizontal_P2.77x2.84mm_EdgePinOffset9.90mm_H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
J3: Conn_02x20_Odd_Even; IDC-Header_2x20_P2.54mm_Vertical
J4: ATX-24; Molex_Mini-Fit_Jr_5566-24A2_2x12_P4.20mm_Vertical
J5: RJ45; RJ45_Amphenol_54602-x08_Horizontal
J6: DIN-5

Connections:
+3.3V: J4.1 (+3.3V), J4.2 (+3.3V), J4.12 (+3.3V), J4.13 (+3.3V)
+5V: J4.4 (+5V), J4.6 (+5V), J4.21 (+5V), J4.22 (+5V), J4.23 (+5V)
+12V: J4.10 (+12V), J4.11 (+12V)
GND: H1.1, H2.1, H3.1, H4.1, J4.3 (GND), J4.5 (GND), J4.7 (GND), J4.15 (GND), J4.17 (GND), J4.18 (GND), J4.19 (GND), J4.24 (GND)

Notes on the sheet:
IDE header
TODO: is this the right pinout/connector gender?

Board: 2 copper layers, 9 parts (0 on the bottom side), 4 nets, no tracks yet.
